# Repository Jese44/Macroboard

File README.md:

# Macroboard
 Macroboard pcb w/ kicad

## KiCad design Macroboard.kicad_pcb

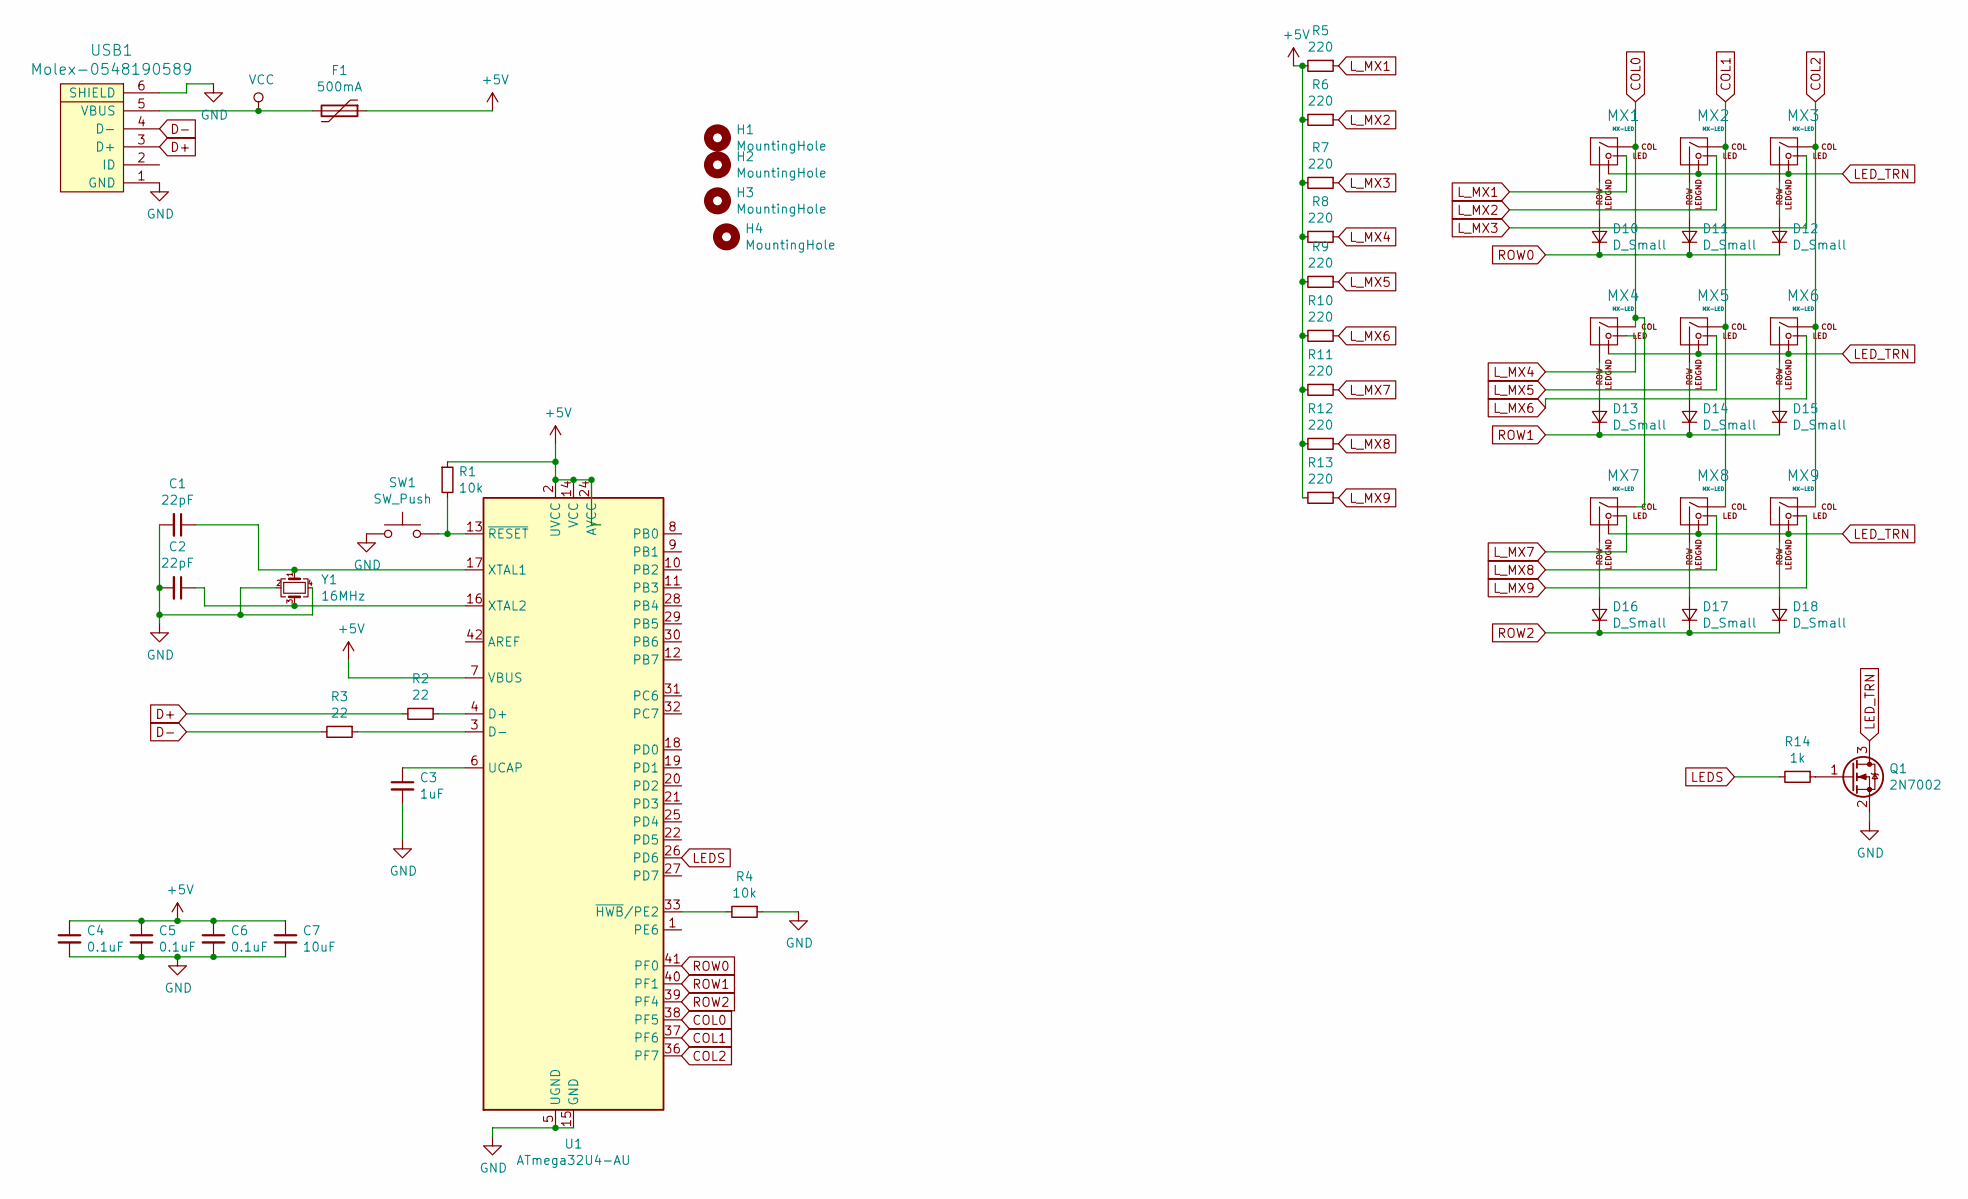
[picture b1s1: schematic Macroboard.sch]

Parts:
C1, C2: 22pF; C_0805_2012Metric_Pad1.15x1.40mm_HandSolder
C3: 1uF; C_0805_2012Metric_Pad1.15x1.40mm_HandSolder
C4, C5, C6: 0.1uF; C_0805_2012Metric_Pad1.15x1.40mm_HandSolder
C7: 10uF; C_0805_2012Metric_Pad1.15x1.40mm_HandSolder
D10, D11, D12, D13, D14, D15, D16, D17, D18: D_Small; D_SOD-123
F1: 500mA; Fuse_1206_3216Metric_Pad1.42x1.75mm_HandSolder
H1, H2, H3, H4: MountingHole; MountingHole_2.2mm_M2_Pad_Via
MX1, MX2, MX3, MX4, MX5, MX6, MX7, MX8, MX9: MX-LED; MXOnly-1U
Q1: 2N7002; SOT-23
R1, R4: 10k; R_0805_2012Metric_Pad1.15x1.40mm_HandSolder
R2, R3: 22; R_0805_2012Metric_Pad1.15x1.40mm_HandSolder
R5, R6, R7, R8, R9, R10, R11, R12, R13: 220; R_0603_1608Metric_Pad1.05x0.95mm_HandSolder
R14: 1k; R_0603_1608Metric_Pad1.05x0.95mm_HandSolder
SW1: SW_Push; SW_PUSH_6mm_H4.3mm
U1: ATmega32U4-AU; TQFP-44_10x10mm_P0.8mm
USB1: Molex-0548190589
Y1: 16MHz; Crystal_SMD_3225-4Pin_3.2x2.5mm_HandSoldering

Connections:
+5V: C4.1, C5.1, C6.1, C7.1, F1.1, R1.1, R5.2, R6.2, R7.2, R8.2, R9.2, R10.2, R11.2, R12.2, R13.2, U1.2 (UVCC), U1.7 (VBUS), U1.14 (VCC), U1.24 (AVCC), U1.34 (VCC), U1.44 (AVCC)
COL0: MX1.1 (COL), MX4.1 (COL), MX7.1 (COL), U1.38 (PF5)
COL1: MX2.1 (COL), MX5.1 (COL), MX8.1 (COL), U1.37 (PF6)
COL2: MX3.1 (COL), MX6.1 (COL), MX9.1 (COL), U1.36 (PF7)
D+: R2.2, USB1.3 (D+)
D-: R3.2, USB1.4 (D-)
GND: C1.2, C2.2, C3.2, C4.2, C5.2, C6.2, C7.2, Q1.2 (S), R4.1, SW1.1, U1.5 (UGND), U1.15 (GND), U1.23 (GND), U1.35 (GND), U1.43 (GND), USB1.1 (GND), USB1.6 (SHIELD), Y1.2, Y1.4
LEDS: R14.2, U1.26 (PD6)
LED_TRN: MX1.4 (LEDGND), MX2.4 (LEDGND), MX3.4 (LEDGND), MX4.4 (LEDGND), MX5.4 (LEDGND), MX6.4 (LEDGND), MX7.4 (LEDGND), MX8.4 (LEDGND), MX9.4 (LEDGND), Q1.3 (D)
L_MX1: MX1.3 (LED), R5.1
L_MX2: MX2.3 (LED), R6.1
L_MX3: MX3.3 (LED), R7.1
L_MX4: MX4.3 (LED), R8.1
L_MX5: MX5.3 (LED), R9.1
L_MX6: MX6.3 (LED), R10.1
L_MX7: MX7.3 (LED), R11.1
L_MX8: MX8.3 (LED), R12.1
L_MX9: MX9.3 (LED), R13.1
unnamed: C1.1, U1.17 (XTAL1), Y1.1
unnamed: C2.1, U1.16 (XTAL2), Y1.3
unnamed: C3.1, U1.6 (UCAP)
unnamed: D10.2 (A), MX1.2 (ROW)
unnamed: D11.2 (A), MX2.2 (ROW)
unnamed: D12.2 (A), MX3.2 (ROW)
unnamed: D13.2 (A), MX4.2 (ROW)
unnamed: D14.2 (A), MX5.2 (ROW)
unnamed: D15.2 (A), MX6.2 (ROW)
unnamed: D16.2 (A), MX7.2 (ROW)
unnamed: D17.2 (A), MX8.2 (ROW)
unnamed: D18.2 (A), MX9.2 (ROW)
unnamed: Q1.1 (G), R14.1
unnamed: R1.2, SW1.2, U1.13 (~RESET)
unnamed: R2.1, U1.4 (D+)
unnamed: R3.1, U1.3 (D-)
unnamed: R4.2, U1.33 (~HWB~/PE2)
ROW0: D10.1 (K), D11.1 (K), D12.1 (K), U1.41 (PF0)
ROW1: D13.1 (K), D14.1 (K), D15.1 (K), U1.40 (PF1)
ROW2: D16.1 (K), D17.1 (K), D18.1 (K), U1.39 (PF4)
VCC: F1.2, USB1.5 (VBUS)

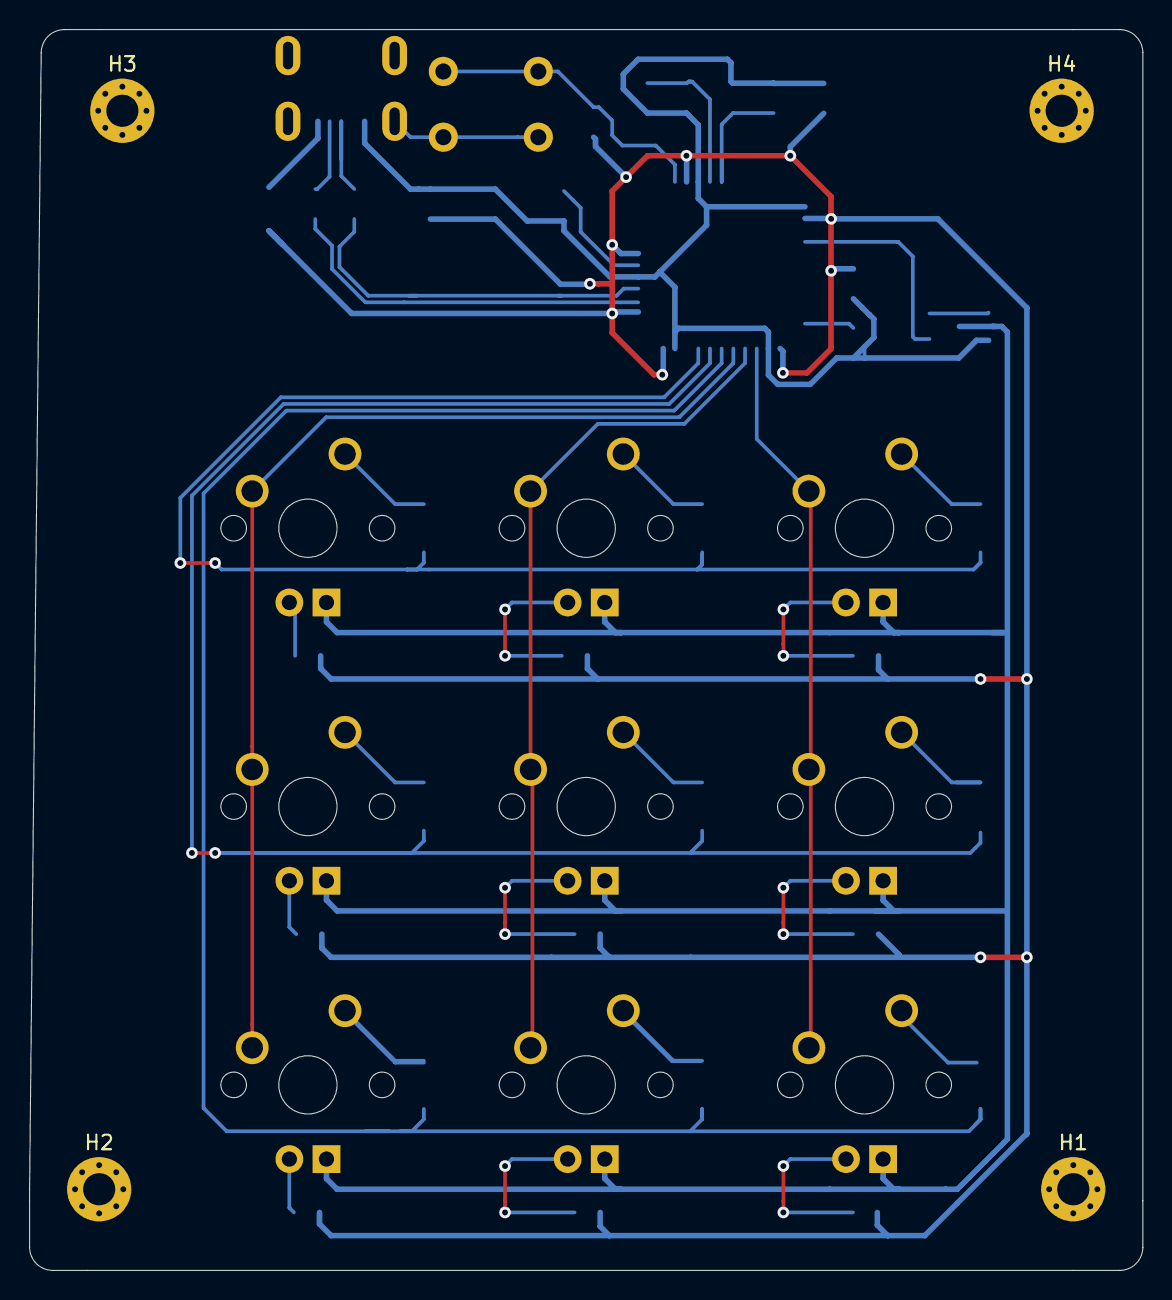
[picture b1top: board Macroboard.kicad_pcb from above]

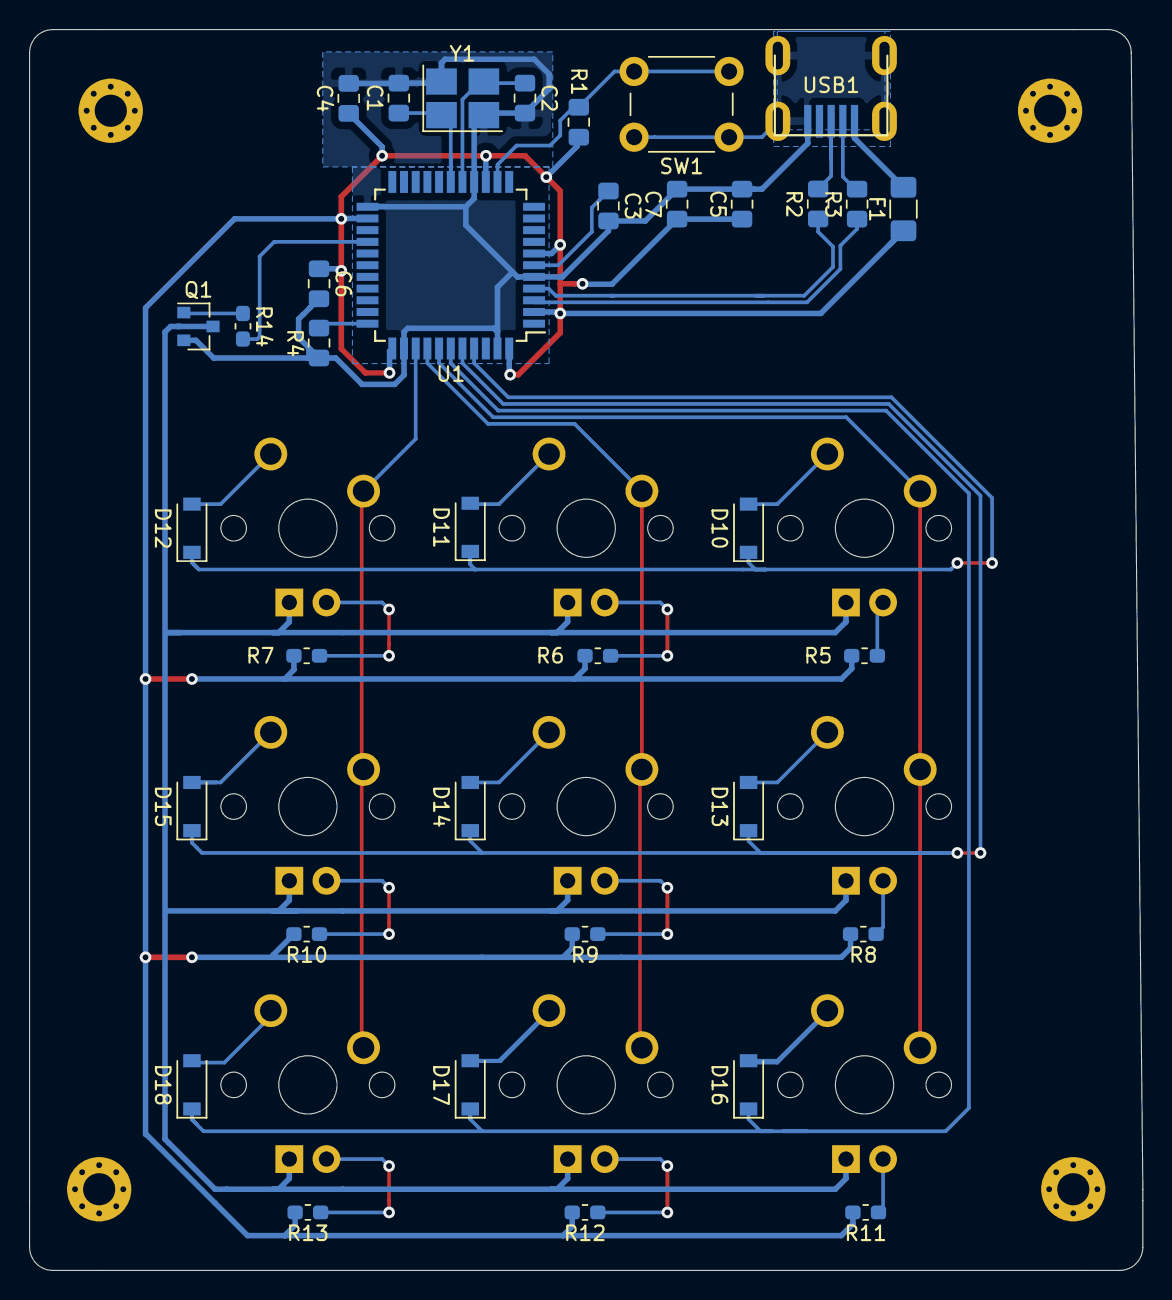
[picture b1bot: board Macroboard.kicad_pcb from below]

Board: 2 copper layers, 76.2 x 84.9 mm, 49 parts (36 on the bottom side), 39 nets.

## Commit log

2019-10-25 Initialixe project
2019-10-25 Add footprint libs
2019-10-25 Schema creation
2019-10-26 pcb base
2019-10-26 PCB v1 done
2019-10-26 mounting holes to PCB
2019-10-26 LED-switches added
2019-10-26 added fet
2019-10-27 new button and hotfixin
2019-10-27 small fixes
